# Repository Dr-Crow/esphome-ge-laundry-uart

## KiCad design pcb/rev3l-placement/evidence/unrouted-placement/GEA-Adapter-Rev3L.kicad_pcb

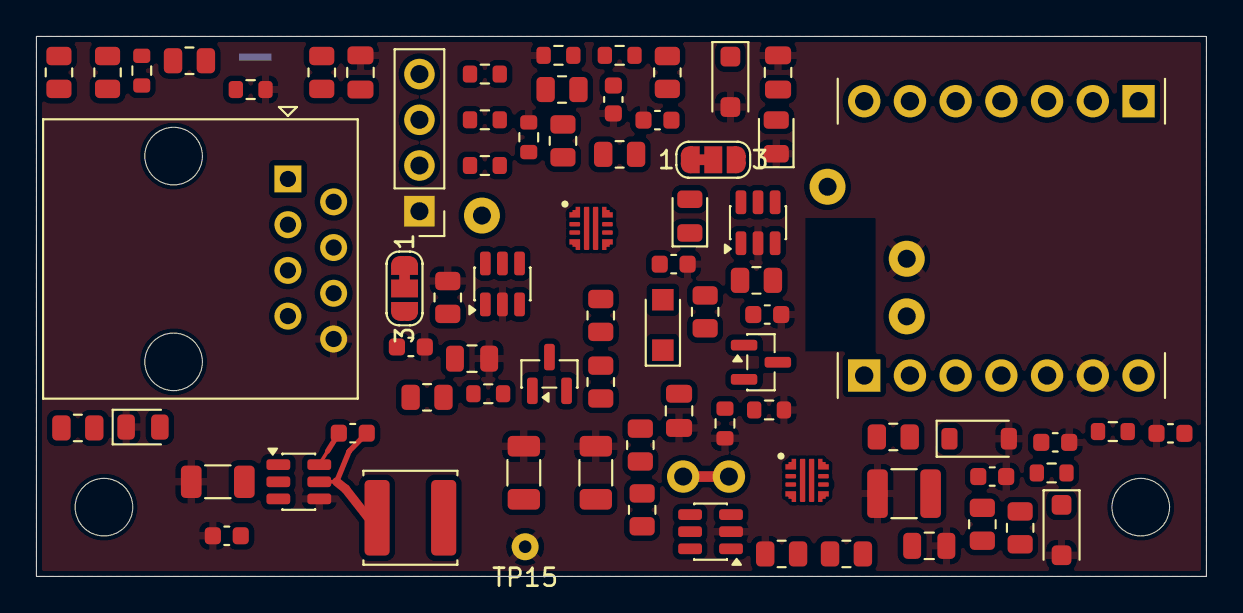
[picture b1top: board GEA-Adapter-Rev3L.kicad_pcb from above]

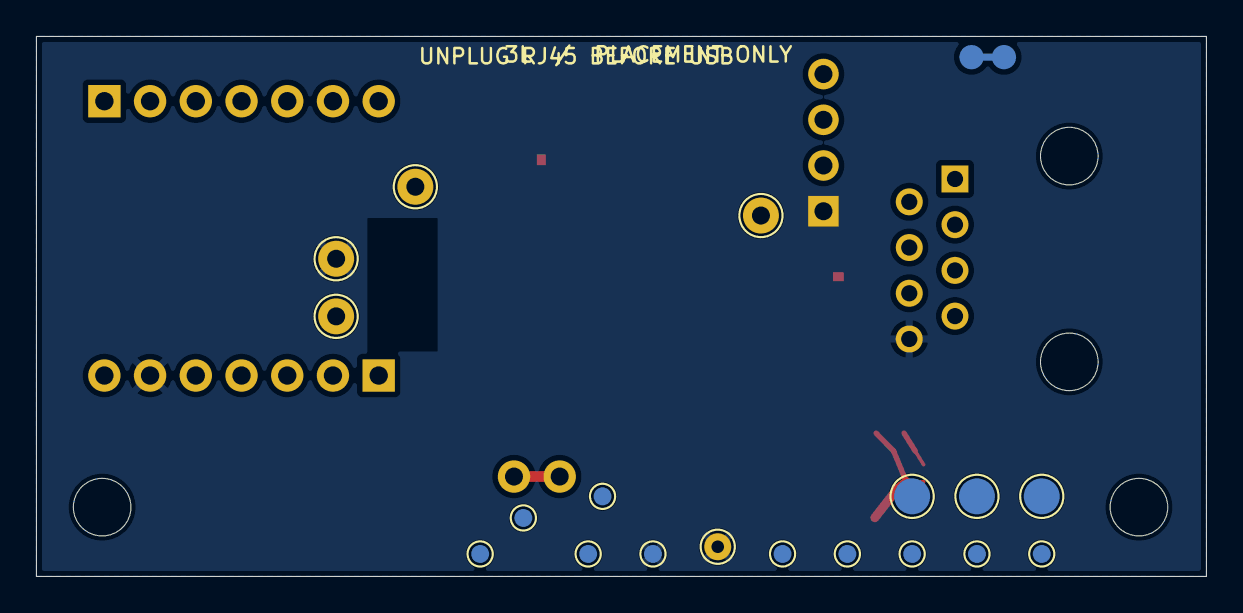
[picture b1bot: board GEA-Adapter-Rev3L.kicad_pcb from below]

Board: 4 copper layers, 65.0 x 30.0 mm, 98 parts (19 on the bottom side), 49 nets.

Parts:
C1, C3, C4, C5, C6, C7, C10, C12, C14, C15: 100n 50V X7R; C_0603_1608Metric
C2: 1u; C_0805_2012Metric
C9: 10u 50V X5R; C_1206_3216Metric
C11, C13: 10u 25V X5R; C_0805_2012Metric
C16, C17: 22u 25V X5R; C_1206_3216Metric
C20, C21: 1u 50V X7R; C_0805_2012Metric
C30: 47u 35V DNP; C_1210_3225Metric
D4: GRN; LED_0805_2012Metric
D5: RED; LED_0805_2012Metric
D6: YLW; LED_0805_2012Metric
D8: DNI; D_SOD-123
D9: BAV99; SOT-23
D11: PMEG2010ER; Nexperia_CFP3_SOD-123W
D18, D20: SMF17A; D_SOD-123F
H1, H2: MountingHole; MountingHole_3.2mm_M3_DIN965
J1: 8P8C; RJ45_EVERCOM_5301-8P8C_Horizontal
J5: Socket_XIAO_A; Socket_1x07_P2.54mm_HCTL_PM254
J6: Socket_XIAO_B; Socket_1x07_P2.54mm_HCTL_PM254
J7: BUS_MON_3V3; PinHeader_1x04_P2.54mm_Vertical
JP1: FirstBuild; SolderJumper-3_P1.3mm_Bridged12_RoundedPad1.0x1.5mm_NumberL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
JP2: GEA3_TX_SEL; SolderJumper-3_P1.3mm_Bridged12_RoundedPad1.0x1.5mm_NumberL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
JP3: 5V_LINK; ServiceLink_NC_P2.54mm
JP4: TX3_ENABLE; SignalLink_NC_P1.8mm
L1: 4.7uH; L_Sunlord_SWPA5040S
Q1: AO3400A; SOT-23
R1, R2, R5, R14, R15, R16, R17, R19, R20: 10K; R_0805_2012Metric
R4, R6, R7: 220; R_0805_2012Metric
R10, R11, R12, R13, R23, R24, R25: 1K; R_0805_2012Metric
R18, R21: 220k; R_0805_2012Metric
R22: 4K7; R_0805_2012Metric
R31, R38: 360k; R_0603_1608Metric
R32: 150k; R_0603_1608Metric
R33, R37: 68k; R_0603_1608Metric
R34, R41: 3.3k; R_0603_1608Metric
R36: 100k; R_0603_1608Metric
R44, R45: 1M; R_0603_1608Metric
R48, R49, R50: 1K; R_0603_1608Metric
TP1, TP2, TP3: TestPoint; TestPoint_Pad_D2.0mm
TP4, TP5, TP6, TP7: TestPoint; TestPoint_THTPad_D2.0mm_Drill1.0mm
TP8: PIN1_IN; TestPoint_Pad_D1.0mm
TP9: PIN3_IN; TestPoint_Pad_D1.0mm
TP10: PIN1_ILM; TestPoint_Pad_D1.0mm
TP11: PIN3_ILM; TestPoint_Pad_D1.0mm
TP12: BUCK_5V; TestPoint_Pad_D1.0mm
TP13: AUXOFF1; TestPoint_Pad_D1.0mm
TP14: PIN3_OV; TestPoint_Pad_D1.0mm
TP15: GND_MUX; TestPoint_THTPad_D1.5mm_Drill0.7mm
TP16: GND_ESD; TestPoint_Pad_D1.0mm
TP17: PIN1_FLT_N; TestPoint_Pad_D1.0mm
TP18: PIN3_FLT_N; TestPoint_Pad_D1.0mm
U4: 74LVC2G07; SOT-23-6
U5: 74LVC2G07_3v3; SOT-23-6
U8: AP63205WU; TSOT-23-6
U9, U10: TPS259470A; TI_RPW0010A_VQFN-HR-10_2x2mm
U11: SRV05-4; SOT-23-6

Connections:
+3V3: C2.1, C4.2, C6.2, C13.1, C14.2, J6.5, R1.2, R2.1, R4.2, R5.2, R14.2, R16.2, R17.2, R36.1, TP2.1, U5.5 (+3V3)
+5V: C1.1, C3.1, C5.1, C7.1, C11.1, C12.2, D8.1 (K), J6.7, JP3.2, R19.2, R20.2, R21.2, TP1.1, U4.5 (VCC), U11.5
/ALT_PWR: C21.1, D20.1, J1.3, Q1.3, R38.1, R45.1, TP9.1, U10.5
/AUXOFF1: Q1.1, R36.2, TP13.1, U9.3
/BOOT_SEL: J6.2, R1.1
/BUCK_5V: C16.1, C17.1, D11.2 (A), L1.2, TP12.1, U8.1 (FB)
/BUCK_BST: C15.1, U8.6 (BST)
/BUCK_SW: C15.2, L1.1, U8.5 (SW)
/D11_K: D11.1 (K), JP3.1
/DBG_LED: D5.1 (K), J5.1, R5.1
/GEA2_MCU_TX: J5.4, JP1.1 (A)
/GEA3_TX_D4: J5.5, JP2.3
/GEA3_TX_D6: J5.7, JP2.1
/LED1: J5.3, R7.2
/LED2: J5.2, R6.1
/PIN1_FLT_N: TP17.1, U9.4
/PIN1_ILM: R34.1, TP10.1, U9.9
/PIN1_OV: R33.1, R44.2, U9.2
/PIN1_UV: R31.2, R32.1, U9.1
/PIN3_FLT_N: TP18.1, U10.4
/PIN3_ILM: R41.1, TP11.1, U10.9
/PIN3_OV: Q1.2, R37.1, R45.2, TP14.1, U10.2
/PIN3_UV: R38.2, U10.1
/V_INPUT: C9.1, C10.2, C30.1, TP3.1, U8.2 (EN), U8.3 (IN), U9.6, U10.6
BOOT: J6.3, JP1.3 (B), R2.2
GEA2_RX: J6.4, R10.1, R48.1
GEA2_TX: JP1.2 (C), R11.1
GEA3_RX: JP2.2, R12.1, R50.1
GEA3_TX: J6.1, R13.1, R49.1
GEA_FullRx: J1.5, R24.2, U11.3
GEA_FullTx: J1.4, R25.2, U11.4
GEA_HalfDplx: J1.7, R23.2, U11.1
GND: C1.2, C2.2, C3.2, C4.1, C5.2, C6.1, C7.2, C9.2, C10.1, C11.2, C12.1, C13.2, C14.1, C16.2, C17.2, C20.2, C21.2, C30.2, D4.1 (K), D6.1 (K), D8.2 (A), D18.2, D20.2, J1.8, J6.6, J7.1, R15.1, R18.2, R32.2, R33.2, R34.2, R37.2, R41.2, TP7.1, TP15.1, TP16.1, U4.2 (GND), U5.2 (GND), U8.4 (GND), U9.8, U10.8, U11.2
unnamed: D4.2 (A), R6.2
unnamed: D5.2 (A), R4.1
unnamed: D6.2 (A), R7.1
unnamed: D9.3 (K), R19.1, R22.1, U5.6
unnamed: D9.2 (A), R18.1, R22.2, R23.1, TP4.1, U4.1
unnamed: J7.2, R48.2
unnamed: J7.3, R49.2
unnamed: J7.4, R50.2
unnamed: JP4.1, U5.4
unnamed: JP4.2, R20.1, R24.1, TP5.1
unnamed: R10.2, R14.1, U4.6
unnamed: R11.2, R15.2, U5.1
unnamed: R12.2, R16.1, U5.3
unnamed: R13.2, R17.1, U4.4
unnamed: R21.1, R25.1, TP6.1, U4.3
VDC: C20.1, D18.1, J1.1, R31.1, R44.1, TP8.1, U9.5
